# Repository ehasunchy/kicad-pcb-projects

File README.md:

# KiCad PCB Design Portfolio

## Featured Project — ESP32 IoT Sensor Controller

A custom-designed, two-layer ESP32 IoT controller PCB
developed in KiCad 10, integrating an ESP32-WROOM-32E,
SHT31 temperature and humidity sensor, CP2102N
USB-to-UART interface, and regulated 3.3V power supply.

**Highlights:**
- Complete schematic and PCB layout
- ERC and DRC passed with 0 errors and 0 warnings
- Fully routed PCB with 0 unrouted connections
- Gerber X2, drill files, component position files, and BOM included
- Design completed; fabrication and physical testing pending

**[Explore the ESP32 IoT Sensor Controller Project](ESP32_IoT_Sensor_Controller/README.md)**

---

**LED indicators · Voltage regulation · NE555 timer · USB-C power · Schematic-to-PCB workflow**

Five PCB design projects, ranging from basic LED circuits and voltage regulators to an ESP32-based IoT sensor controller, with editable KiCad sources, design previews, and available manufacturing documentation.

## Projects

| Project | Scope |
| :--- | :--- |
| [ESP32 IoT Sensor Controller](ESP32_IoT_Sensor_Controller/README.md) | Two-layer ESP32 IoT PCB featuring SHT31 sensing, CP2102N USB-UART, 3.3V regulation, design verification, BOM, and manufacturing outputs. |
| [LED Basic Board](LED_Basic_Board/README.md) | A three-footprint LED indicator practice board with a 330-ohm resistor and two-pin connector. |
| [5V to 3V3 LDO Board](5V_to_3V3_LDO_Board/README.md) | A seven-footprint AMS1117-3.3 regulator practice board with capacitors, input/output connectors, and an LED indicator. |
| [NE555 Astable LED Blinker](555_Timer_LED_Blinker/README.md) | A 5V timer-based LED blinker with editable source, Gerbers, drill exports, and previews. |
| [USB-C 3.3V Interface Board](USB_C_3V3_Interface_Board/README.md) | A USB-C-powered AP2112K-3.3 regulator board with I²C/GPIO headers, BOM, manufacturing outputs and current checks with disclosed exclusions. |

## Open a design

Open the corresponding `.kicad_pro` in KiCad 10.0. Open KiCad_Project/ inside the selected project. Supplied Gerbers and drill files are browsable under Manufacturing/, with unchanged original complete ZIPs under Archives/.

## Use and validation

Open editable project files in their original CAD application. The archives preserve project subfolders; extract an archive before opening its project. External libraries or 3D-model paths may need to be remapped on another computer.

These are portfolio design files. Existing reports are snapshots from their recorded dates; fabrication exports are not evidence of manufactured or bench-tested hardware. Review the design and rerun the checks before fabrication.

No blanket license is assigned. Third-party components, libraries, and tutorial material retain their original rights and terms.

## Repository organization

Each project guide links to its editable sources, available outputs and recorded status. Original project archives remain unchanged. [Reorganization record](Documentation/REORGANIZATION.md) documents preservation and path changes.

## Related portfolios

- [KiCad PCB projects](https://github.com/ehasunchy/kicad-pcb-projects)
- [Altium PCB projects](https://github.com/ehasunchy/altium-pcb-projects)
- [AutoCAD Electrical projects](https://github.com/ehasunchy/autocad-electrical-projects)

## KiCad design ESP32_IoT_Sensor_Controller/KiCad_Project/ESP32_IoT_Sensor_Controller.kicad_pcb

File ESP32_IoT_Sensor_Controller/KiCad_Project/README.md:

# KiCad Source Files

This folder contains the editable KiCad 10 project files for the ESP32 IoT Sensor Controller, including the schematic, PCB layout, project configuration, and custom symbol and footprint libraries.

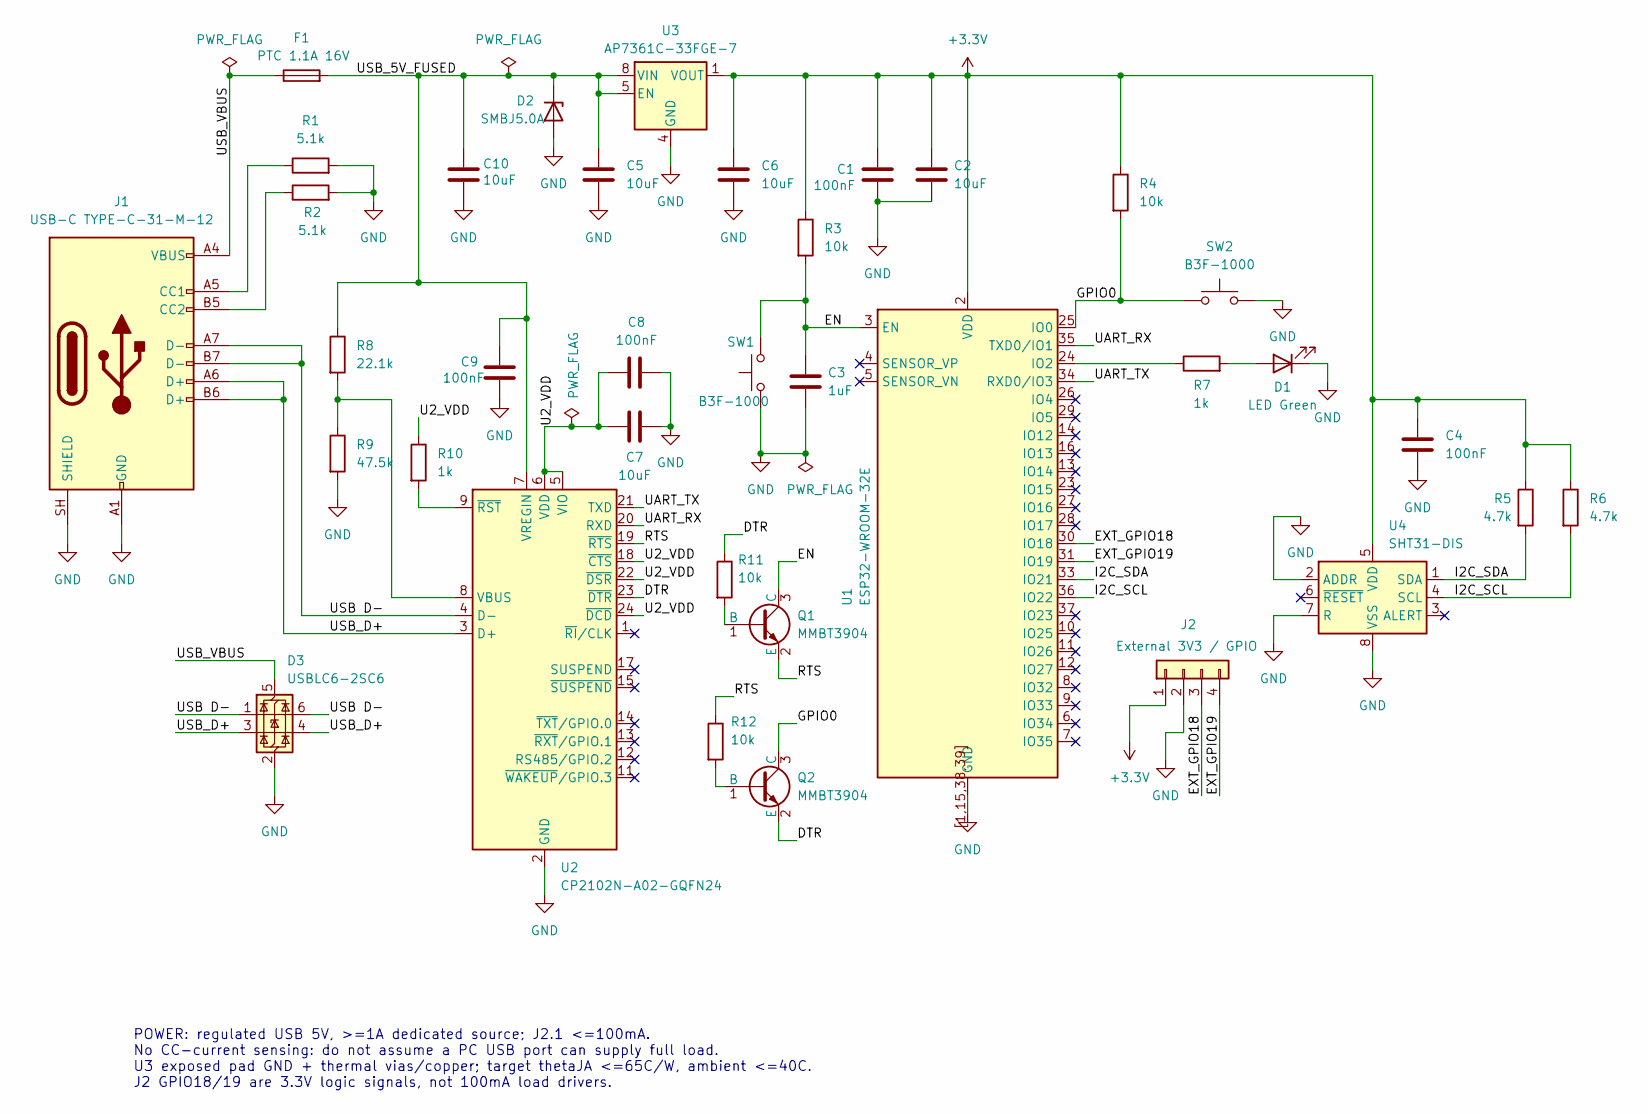
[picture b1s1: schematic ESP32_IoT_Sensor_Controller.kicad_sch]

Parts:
C1, C4, C8, C9: 100nF; C_0603_1608Metric; Rating 50V X7R +/-10%; MPN C1608X7R1H104K080AA
C2, C5, C6, C7: 10uF; C_1206_3216Metric; Rating 25V X7R +/-10%; verify effective >=4.7u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; MPN CL31B106KAHNNNE
C3: 1uF; C_0603_1608Metric; Rating 10V X5R +/-10%; MPN C1608X5R1A105K080AC
C10: 10uF; C_1206_3216Metric; Rating 25V X7R +/-10%; local VREGIN bulk; MPN CL31B106KAHNNNE
D1: LED Green; LED_0603_1608Metric; Rating 0603 1K 2A; MPN APT1608SGC
D2: SMBJ5.0A; D_SMB; Rating 5V standoff; ESD/surge only, NOT sustai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; MPN SMBJ5.0A-TR
D3: USBLC6-2SC6; SOT-23-6; Rating SOT23-6 USB ESD; MPN USBLC6-2SC6
F1: PTC 1.1A 16V; Fuse_1206_3216Metric; Rating Ihold1.1A at20C; 0.92A at40C; MPN 1206L110/16WR
J1: USB-C TYPE-C-31-M-12; USB_C_HRO_Custom; Rating USB2.0 16-contact; A8/B8 unused; MPN TYPE-C-31-M-12
J2: External 3V3 / GPIO; PinHeader_1x04_P2.54mm_Vertical; Rating 2.54mm 1x4; J2.1 max100mA, GPIO only si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; MPN TSW-104-07-G-S
Q1, Q2: MMBT3904; SOT-23; Rating SOT23 1B 2E 3C; MPN MMBT3904LT1G
R1, R2: 5.1k; R_0603_1608Metric; Rating 1% 0.1W 0603; MPN RC0603FR-075K1L
R3, R4, R11, R12: 10k; R_0603_1608Metric; Rating 1% 0.1W 0603; MPN RC0603FR-0710KL
R5, R6: 4.7k; R_0603_1608Metric; Rating 1% 0.1W 0603; MPN RC0603FR-074K7L
R7, R10: 1k; R_0603_1608Metric; Rating 1% 0.1W 0603; MPN RC0603FR-071KL
R8: 22.1k; R_0603_1608Metric; Rating 1% 0.1W 0603; MPN RC0603FR-0722K1L
R9: 47.5k; R_0603_1608Metric; Rating 1% 0.1W 0603; MPN RC0603FR-0747K5L
SW1, SW2: B3F-1000; SW_PUSH_6mm; Rating SPST-NO; same-net pairs 1/1 and 2/2; MPN B3F-1000
U1: ESP32-WROOM-32E; ESP32-WROOM-32E_Custom; Rating 4MB flash PCB antenna; MPN ESP32-WROOM-32E-N4
U2: CP2102N-A02-GQFN24; QFN24_4x4mm_P0.5mm_CP2102N; Rating QFN24 EP25 GND; MPN CP2102N-A02-GQFN24R
U3: AP7361C-33FGE-7; AP7361C_UDFN3030_8E; Rating 3.3V 1A; thermal copper and vias requir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; MPN AP7361C-33FGE-7
U4: SHT31-DIS; Sensirion_DFN-8-1EP_2.5x2.5mm_P0.5mm_EP1.1x1.7mm; Rating DFN8 EP9 GND; I2C address 0x44; MPN SHT31-DIS-B

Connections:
+3.3V: C1.1, C2.1, C4.1, C6.1, J2.1, R3.1, R4.1, R5.1, R6.1, U1.2 (VDD), U3.1 (VOUT), U4.5 (VDD)
/DTR: Q2.2 (E), R11.1, U2.23 (~DTR)
/EN: C3.1, Q1.3 (C), R3.2, SW1.2, U1.3 (EN)
/EXT_GPIO18: J2.3, U1.30 (IO18)
/EXT_GPIO19: J2.4, U1.31 (IO19)
/GPIO0: Q2.3 (C), R4.2, SW2.1, U1.25 (IO0)
/I2C_SCL: R6.2, U1.36 (IO22), U4.4 (SCL)
/I2C_SDA: R5.2, U1.33 (IO21), U4.1 (SDA)
/RTS: Q1.2 (E), R12.1, U2.19 (~RTS)
/U2_VDD: C7.1, C8.1, R10.1, U2.5 (VIO), U2.6 (VDD), U2.18 (~CTS), U2.22 (~DSR), U2.24 (~DCD)
/UART_RX: U1.35 (TXD0/IO1), U2.20 (RXD)
/UART_TX: U1.34 (RXD0/IO3), U2.21 (TXD)
/USB D−: D3.1 (I/O1), D3.6 (I/O1), J1.A7 (D-), J1.B7 (D-), U2.4 (D-)
/USB_5V_FUSED: C5.1, C9.1, C10.1, D2.1 (K), F1.2, R8.1, U2.7 (VREGIN), U3.5 (EN), U3.8 (VIN)
/USB_D+: D3.3 (I/O2), D3.4 (I/O2), J1.A6 (D+), J1.B6 (D+), U2.3 (D+)
/USB_VBUS: D3.5 (VBUS), F1.1, J1.A4 (VBUS), J1.A9 (VBUS), J1.B4 (VBUS), J1.B9 (VBUS)
GND: C1.2, C2.2, C3.2, C4.2, C5.2, C6.2, C7.2, C8.2, C9.2, C10.2, D1.1 (K), D2.2 (A), D3.2 (GND), J1.A1 (GND), J1.A12 (GND), J1.B1 (GND), J1.B12 (GND), J1.SH (SHIELD), J2.2, R1.2, R2.2, R9.2, SW1.1, SW2.2, U1.1 (GND), U1.15 (GND), U1.38 (GND), U1.39 (GND), U1.[1,15,38,39] (GND), U2.2 (GND), U2.25 (GND), U3.4 (GND), U3.9 (EP_GND), U4.2 (ADDR), U4.7 (R), U4.8 (VSS), U4.9 (VSS)
unnamed: D1.2 (A), R7.2
unnamed: J1.A5 (CC1), R1.1
unnamed: J1.B5 (CC2), R2.1
unnamed: Q1.1 (B), R11.2
unnamed: Q2.1 (B), R12.2
unnamed: R7.1, U1.24 (IO2)
unnamed: R8.2, R9.1, U2.8 (VBUS)
unnamed: R10.2, U2.9 (~RST)

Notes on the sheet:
POWER: regulated USB 5V, >=1A dedicated source; J2.1 <=100mA. No CC-current sensing: do not assume a PC USB port can supply full load. U3 exposed pad GND + thermal vias/copper; target thetaJA <=65C/W, ambient <=40C. J2 GPIO18/19 are 3.3V logic signals, not 100mA load drivers.

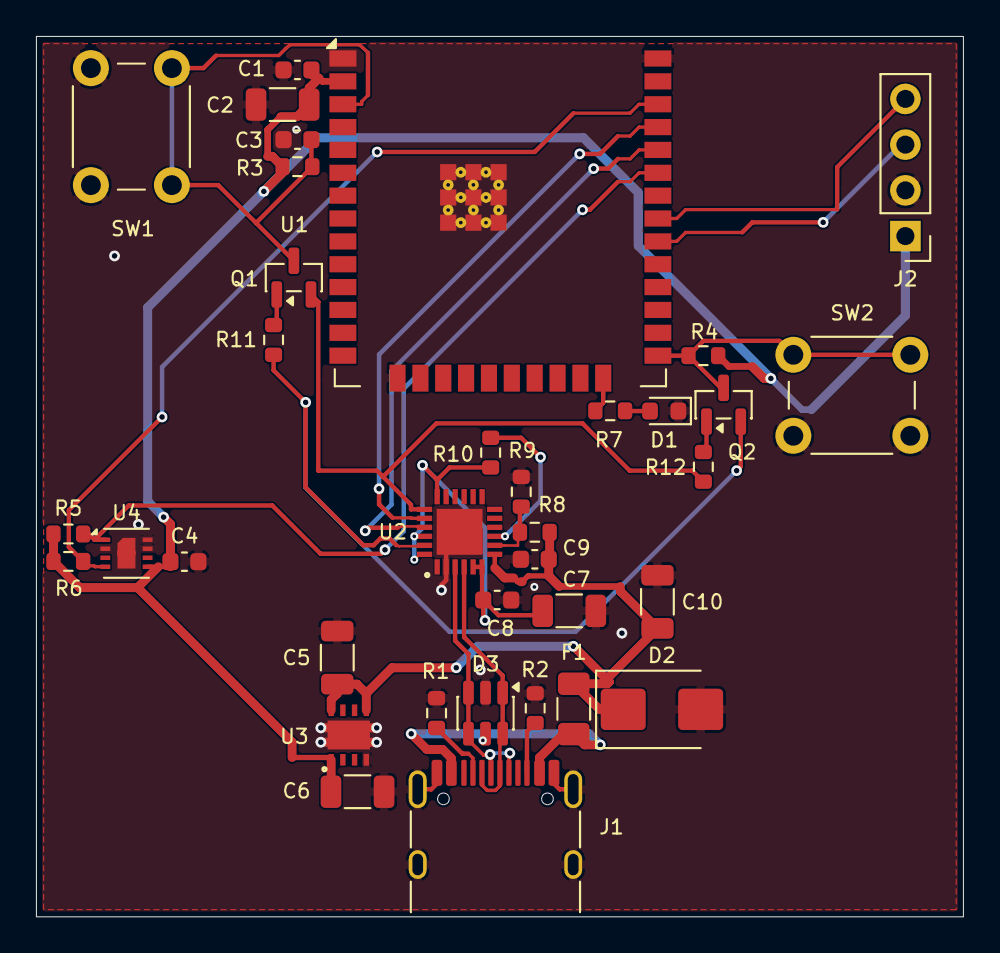
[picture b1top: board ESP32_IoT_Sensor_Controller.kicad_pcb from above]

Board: 2 copper layers, 51.5 x 48.9 mm, 36 parts (0 on the bottom side), 25 nets.

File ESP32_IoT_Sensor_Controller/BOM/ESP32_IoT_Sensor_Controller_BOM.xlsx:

ESP32 IoT Sensor Controller — Bill of Materials
Project: ESP32_IoT_Sensor_Controller
Design Tool: KiCad 10 | PCB: 2-Layer
Status: Design completed; manufacturing and physical testing pending
Total quantity / board | 36
Reference | Qty | Value | Footprint | Datasheet | Manufacturer | MPN
C1,C4,C8,C9 | 4 | 100nF | Capacitor_SMD:C_0603_1608Metric | Datasheet | TDK | C1608X7R1H104K080AA
C2,C5,C6,C7,C10 | 5 | 10uF | Capacitor_SMD:C_1206_3216Metric | Datasheet | Samsung Electro-Mechanics | CL31B106KAHNNNE
C3 | 1 | 1uF | Capacitor_SMD:C_0603_1608Metric | Datasheet | TDK | C1608X5R1A105K080AC
D1 | 1 | LED Green | LED_SMD:LED_0603_1608Metric | Datasheet | Kingbright | APT1608SGC
D2 | 1 | SMBJ5.0A | Diode_SMD:D_SMB | Datasheet | STMicroelectronics | SMBJ5.0A-TR
D3 | 1 | USBLC6-2SC6 | Package_TO_SOT_SMD:SOT-23-6 | Datasheet | STMicroelectronics | USBLC6-2SC6
F1 | 1 | PTC 1.1A 16V | Fuse:Fuse_1206_3216Metric | Datasheet | Littelfuse | 1206L110/16WR
J1 | 1 | USB-C TYPE-C-31-M-12 | ESP32_IoT_Custom:USB_C_HRO_Custom | Datasheet | HRO | TYPE-C-31-M-12
J2 | 1 | External 3V3 / GPIO | Connector_PinHeader_2.54mm:PinHeader_1x04_P2.54mm_Vertical | Datasheet | Samtec | TSW-104-07-G-S
Q1,Q2 | 2 | MMBT3904 | Package_TO_SOT_SMD:SOT-23 | Datasheet | onsemi | MMBT3904LT1G
R1,R2 | 2 | 5.1k | Resistor_SMD:R_0603_1608Metric | Datasheet | YAGEO | RC0603FR-075K1L
R3,R4,R11,R12 | 4 | 10k | Resistor_SMD:R_0603_1608Metric | Datasheet | YAGEO | RC0603FR-0710KL
R5,R6 | 2 | 4.7k | Resistor_SMD:R_0603_1608Metric | Datasheet | YAGEO | RC0603FR-074K7L
R7,R10 | 2 | 1k | Resistor_SMD:R_0603_1608Metric | Datasheet | YAGEO | RC0603FR-071KL
R8 | 1 | 22.1k | Resistor_SMD:R_0603_1608Metric | Datasheet | YAGEO | RC0603FR-0722K1L
R9 | 1 | 47.5k | Resistor_SMD:R_0603_1608Metric | Datasheet | YAGEO | RC0603FR-0747K5L
SW1,SW2 | 2 | B3F-1000 | Button_Switch_THT:SW_PUSH_6mm | Datasheet | Omron | B3F-1000
U1 | 1 | ESP32-WROOM-32E | ESP32_IoT_Custom:ESP32-WROOM-32E_Custom | Datasheet | Espressif | ESP32-WROOM-32E-N4
U2 | 1 | CP2102N-A02-GQFN24 | Controller:QFN24_4x4mm_P0.5mm_CP2102N | Datasheet | Silicon Labs | CP2102N-A02-GQFN24R
U3 | 1 | AP7361C-33FGE-7 | Controller:AP7361C_UDFN3030_8E | Datasheet | Diodes Incorporated | AP7361C-33FGE-7
U4 | 1 | SHT31-DIS | Sensor_Humidity:Sensirion_DFN-8-1EP_2.5x2.5mm_P0.5mm_EP1.1x1.7mm | Datasheet | Sensirion | SHT31-DIS-B
0 | 0 | 0 | 0 |  | 0 | 0
0 | 0 | 0 | 0 |  | 0 | 0
0 | 0 | 0 | 0 |  | 0 | 0
0 | 0 | 0 | 0 |  | 0 | 0
0 | 0 | 0 | 0 |  | 0 | 0
0 | 0 | 0 | 0 |  | 0 | 0
0 | 0 | 0 | 0 |  | 0 | 0
0 | 0 | 0 | 0 |  | 0 | 0
0 | 0 | 0 | 0 |  | 0 | 0

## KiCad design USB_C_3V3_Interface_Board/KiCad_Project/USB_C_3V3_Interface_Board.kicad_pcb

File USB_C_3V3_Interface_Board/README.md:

# USB-C 3.3V Interface Board

**A compact two-layer KiCad practice PCB for USB-C 5V power input, nominal 3.3V regulation and I²C/GPIO header connections.**

## Project overview

The board accepts nominal 5V power through a USB-C receptacle and uses an AP2112K-3.3 LDO to supply external low-power electronics. Separate 5.1kΩ CC pull-down resistors implement a USB-C power sink. USB data transfer and USB Power Delivery negotiation are not implemented.

The I²C and GPIO headers provide connections only. There is no onboard microcontroller or I²C controller. SDA/SCL each have a 4.7kΩ pull-up to 3.3V; GPIO1/GPIO2 each terminate at a single header pin and are not driven on this board.

## Technical specifications

| Parameter | Specification |
| :--- | :--- |
| CAD application | KiCad 10.0; exports/checks generated with 10.0.6 |
| Board outline | 22 × 25.5 mm, measured between outline centerlines |
| Copper layers | 2: F.Cu and B.Cu |
| Nominal input | 5V DC via USB-C |
| Nominal regulated output | 3.3V DC |
| Regulator | AP2112K-3.3 |
| Input protection components | 500mA-rated resettable polyfuse and PESD5V0S1UA TVS |
| Interfaces | Two 1×4 headers for I²C and GPIO connections |
| Layout | Top-side components/routing and bottom-layer GND copper zone |
| Manufacturing outputs | Seven Gerbers, PTH/NPTH Excellon drills and Gerber job file |

The fuse rating does not establish a guaranteed continuous output current. Available output current depends on regulator dissipation, PCB thermal conditions, ambient temperature and component ratings.

## Main components

| Reference | Component/value | Purpose |
| :--- | :--- | :--- |
| J1 | GCT USB4105 USB-C receptacle | Power input |
| R1, R2 | 5.1kΩ | CC1/CC2 pull-down resistors |
| F1 | 500mA resettable polyfuse | Input protection component |
| D1 | PESD5V0S1UA | TVS protection component |
| U1 | AP2112K-3.3 | Nominal 3.3V regulation |
| C1, C2 | 1µF | Input/output decoupling |
| R3, D2 | 1kΩ and green LED | Power indication |
| R4, R5 | 4.7kΩ | SDA/SCL pull-ups |
| J2, J3 | 1×4, 2.54mm headers | External connections |

[BOM CSV](BOM/USB_C_3V3_Interface_Board.csv) contains ten grouped rows covering fourteen components, including footprints and manufacturer/MPN fields. Values, quantities, references and fields were checked against the exported schematic netlist. These checks do not establish component availability or suitability for every operating condition.

## Connector pinouts

| Pin | J2 — I²C | J3 — GPIO |
| :---: | :--- | :--- |
| 1 | +3V3 | +3V3 |
| 2 | GND | GND |
| 3 | SDA | GPIO1 |
| 4 | SCL | GPIO2 |

Pinouts were checked against the schematic netlist. Use the source schematic when connecting external hardware.

## Project files

| Folder | Contents |
| :--- | :--- |
| [KiCad_Project](KiCad_Project/) | Editable project, schematic and PCB |
| [Images](Images/) | Schematic SVG, large top/bottom layout PNG/SVG and 3D preview |
| [Reports](Reports/README.md) | Current ERC/DRC JSON and validation notes |
| [BOM](BOM/USB_C_3V3_Interface_Board.csv) | Component list |
| [Manufacturing](Manufacturing/README.md) | Supplied Gerber/drill exports and download package |
| [Archives](Archives/) | Source/BOM/manufacturing snapshot ZIP |

Open [USB_C_3V3_Interface_Board.kicad_pro](KiCad_Project/USB_C_3V3_Interface_Board.kicad_pro) in KiCad 10.0. Footprints and 3D models use standard KiCad libraries; preview renders depend on the installed model libraries. Temporary lock files, local UI preferences and editor history are not part of the portfolio upload.

## Design verification — 2026-10-09

- [DRC](Reports/DRC.json): zero non-excluded violations, zero unconnected items and zero schematic-parity findings under the saved project settings. **Four excluded USB-C pad-to-NPTH hole-clearance errors remain**: actual clearance 0.1944mm versus the configured 0.2500mm requirement.
- [ERC](Reports/ERC.json): zero error-severity records. The all-severity export contains four warning records for two unique GPIO label findings: GPIO1/GPIO2 each appear once normally and once as excluded. These signals each connect to only one header pin. This is disclosed rather than presented as a zero-warning ERC result.
- Reports include the saved settings' ignored-check lists. Exclusions and disabled checks limit the scope of a clean result.
- BOM fields and header pinouts were compared with the source netlist. Schematic, PCB and 3D previews were generated from the saved source snapshot.

No physical fabrication, assembly, load testing, thermal testing or ESD testing is documented. The connector hole clearances require fabrication review. TVS working/clamping voltage and regulator thermal capability still require operating-condition validation. Manufacturing outputs are supplied exports, not a fabrication approval.

## Project images

### Schematic

### PCB layout

[Zoomable top SVG](Images/pcb-layout.svg)

[Zoomable bottom SVG](Images/pcb-layout-bottom.svg)

Top and bottom copper are shown separately so the bottom ground fill does not cover top routing. The bottom view is mirrored to represent looking from below. Both layout PNGs are 1000 × 1280 pixels; SVG versions retain scalable detail. The 3D image above is a generated preview, not a photograph of assembled hardware.

## Author

**Ehasan Alam Chowdhury** — Electrical & Electronic Engineering (EEE)

GitHub: [ehasunchy](https://github.com/ehasunchy)

Part of a practical PCB design portfolio. [Return to the KiCad portfolio](../README.md).

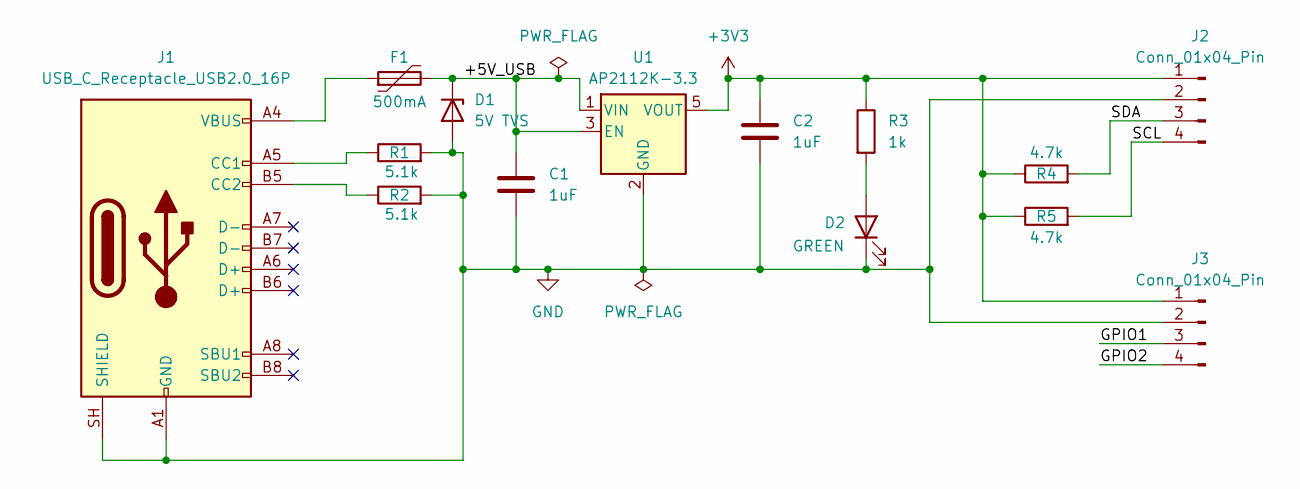
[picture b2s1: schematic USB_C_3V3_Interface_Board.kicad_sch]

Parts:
C1, C2: 1uF; C_0805_2012Metric; MPN GRM21BR71C105KA01L
D1: 5V TVS; D_SOD-323; MPN PESD5V0S1UA,115
D2: GREEN; LED_0805_2012Metric; MPN APT2012LZGCK
F1: 500mA; Fuse_1206_3216Metric; MPN 1206L050/15YR
J1: USB_C_Receptacle_USB2.0_16P; USB_C_Receptacle_GCT_USB4105-xx-A_16P_TopMnt_Horizontal; MPN USB4105-GF-A-120
J2, J3: Conn_01x04_Pin; PinHeader_1x04_P2.54mm_Vertical; MPN 61300411121
R1, R2: 5.1k; R_0805_2012Metric; MPN RC0805FR-075K1L
R3: 1k; R_0805_2012Metric; MPN RC0805FR-071KL
R4, R5: 4.7k; R_0805_2012Metric; MPN RC0805FR-074K7L
U1: AP2112K-3.3; SOT-23-5; MPN AP2112K-3.3TRG1

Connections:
+3V3: C2.1, J2.1, J3.1, R3.1, R4.1, R5.1, U1.5 (VOUT)
/+5V_USB: C1.1, D1.1 (K), F1.2, U1.1 (VIN), U1.3 (EN)
/GPIO1: J3.3
/GPIO2: J3.4
/SCL: J2.4, R5.2
/SDA: J2.3, R4.2
GND: C1.2, C2.2, D1.2 (A), D2.1 (K), J1.A1 (GND), J1.A12 (GND), J1.B1 (GND), J1.B12 (GND), J1.SH (SHIELD), J2.2, J3.2, R1.2, R2.2, U1.2 (GND)
unnamed: D2.2 (A), R3.2
unnamed: F1.1, J1.A4 (VBUS), J1.A9 (VBUS), J1.B4 (VBUS), J1.B9 (VBUS)
unnamed: J1.A5 (CC1), R1.1
unnamed: J1.B5 (CC2), R2.1

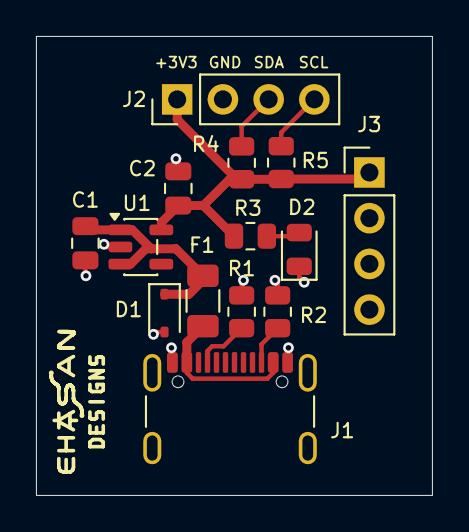
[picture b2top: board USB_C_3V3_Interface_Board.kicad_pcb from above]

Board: 2 copper layers, 22.0 x 25.5 mm, 14 parts (0 on the bottom side), 9 nets.

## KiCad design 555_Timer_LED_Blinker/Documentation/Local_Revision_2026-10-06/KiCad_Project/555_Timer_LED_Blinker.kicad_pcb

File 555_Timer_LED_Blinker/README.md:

# NE555 Astable LED Blinker

A 5V LED blinker designed in KiCad 10.0 using an NE555P timer in astable mode. The schematic includes a 10k/100k timing resistor network, a 10uF timing capacitor, a 1k LED resistor, 100uF supply decoupling, and 10nF control-pin bypassing.

## Files

- Editable KiCad project, schematic, and PCB source files in the project source folder
- [Complete project archive](Archives/555_Timer_LED_Blinker.zip), including the supplied Gerber and drill exports
- PNG and SVG previews generated from the source with KiCad 10.0

## Design status

The preserved KiCad 10.0.6 reports dated 2026-10-05 reported **0 DRC violations, 0 unconnected items, 0 schematic parity issues, and 0 ERC violations** under the supplied project settings. The JSON reports record ignored checks and included severities; this does not establish hardware testing. The supplied fabrication exports are preserved as provided.

- [DRC report](Reports/555_Timer_LED_Blinker-DRC.json)
- [ERC report](Reports/555_Timer_LED_Blinker-ERC.json)

## Browse this project

Open [555_Timer_LED_Blinker.kicad_pro](KiCad_Project/555_Timer_LED_Blinker.kicad_pro) in KiCad 10. Download or clone the whole repository to keep related files together.

| Folder | Contents |
| :--- | :--- |
| [Archives/](Archives/) | Unchanged original complete project ZIP |
| [Documentation/](Documentation/) | Supporting documentation and preserved source-reference snapshots |
| [Images/](Images/) | Existing schematic and board previews |
| [KiCad_Project/](KiCad_Project/) | Editable project, schematic and PCB files |
| [Manufacturing/](Manufacturing/) | Existing fabrication, drill and assembly outputs |
| [Reports/](Reports/) | Saved design-check reports |

## BOM and later local manufacturing revision

The recovered [BOM CSV](BOM/555_Timer_LED_Blinker.csv) contains 9 grouped rows and 10 components, including J1/J2 grouped as quantity 2. Manufacturer and MPN fields are supplied project metadata; purchasing suitability is not established.

The OneDrive local revision has added schematic BOM fields and changes to the PCB outline, capacitor placement and routing. It is preserved as a separate [local source snapshot](Documentation/Local_Revision_2026-10-06/KiCad_Project/) with its [local Gerber/drill files](Manufacturing/Local_Revision_2026-10-06/Gerbers/). The primary `KiCad_Project/`, previews and 2026-10-05 reports remain the existing GitHub revision. The old reports do not validate the later local revision. See [manufacturing documentation](Manufacturing/README.md) before choosing an output set.

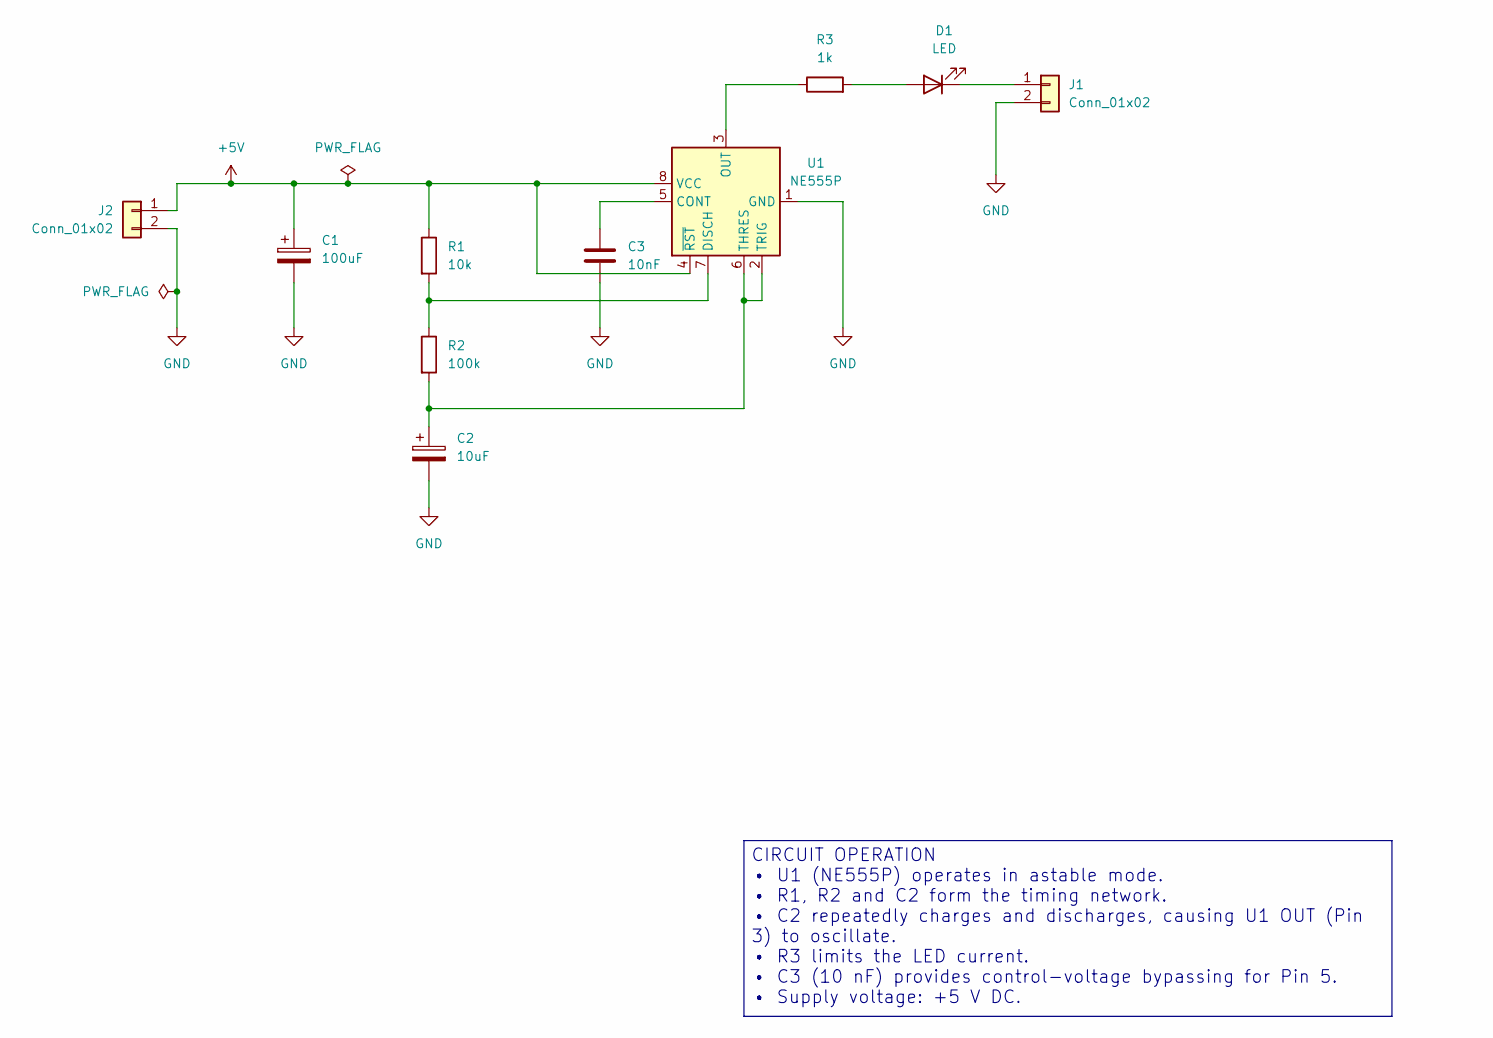
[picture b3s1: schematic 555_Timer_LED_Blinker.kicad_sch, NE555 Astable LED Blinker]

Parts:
C1: 100uF; CP_Elec_6.3x5.8; MPN UWT0J101MCL1GB
C2: 10uF; CP_Elec_4x5.8; MPN UWT1C100MCL1GB
C3: 10nF; C_0805_2012Metric; MPN CC0805KRX7R9BB103
D1: LED; LED_0805_2012Metric; MPN APT2012SURCK
J1, J2: Conn_01x02; PinHeader_1x02_P2.54mm_Vertical; MPN 61300211121
R1: 10k; R_0805_2012Metric; MPN RC0805FR-0710KL
R2: 100k; R_0805_2012Metric; MPN RC0805FR-07100KL
R3: 1k; R_0805_2012Metric; MPN RC0805FR-071KL
U1: NE555P; DIP-8_W7.62mm; MPN NE555P

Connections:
+5V: C1.1, J2.1, R1.1, U1.4 (~RST), U1.8 (VCC)
GND: C1.2, C2.2, C3.2, J1.2, J2.2, U1.1 (GND)
unnamed: D1.2 (A), R3.2
unnamed: D1.1 (K), J1.1
unnamed: C3.1, U1.5 (CONT)
unnamed: R1.2, R2.1, U1.7 (DISCH)
unnamed: R3.1, U1.3 (OUT)
unnamed: C2.1, R2.2, U1.2 (TRIG), U1.6 (THRES)

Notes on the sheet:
CIRCUIT OPERATION • U1 (NE555P) operates in astable mode. • R1, R2 and C2 form the timing network. • C2 repeatedly charges and discharges, causing U1 OUT (Pin 3) to oscillate. • R3 limits the LED current. • C3 (10 nF) provides control-voltage bypassing for Pin 5. • Supply voltage: +5 V DC.

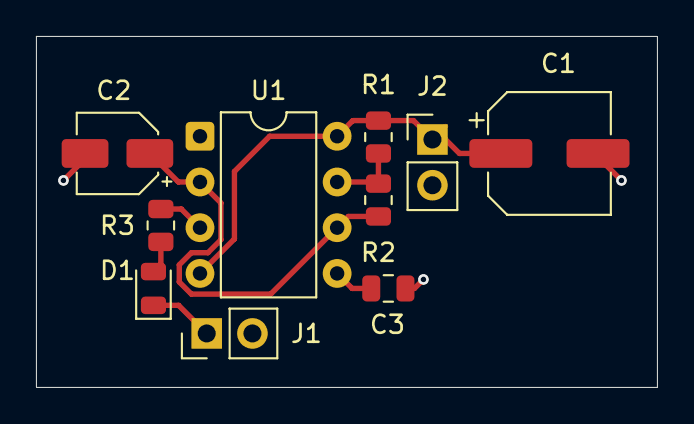
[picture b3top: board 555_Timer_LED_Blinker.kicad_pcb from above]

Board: 2 copper layers, 34.5 x 19.5 mm, 10 parts (0 on the bottom side), 8 nets.

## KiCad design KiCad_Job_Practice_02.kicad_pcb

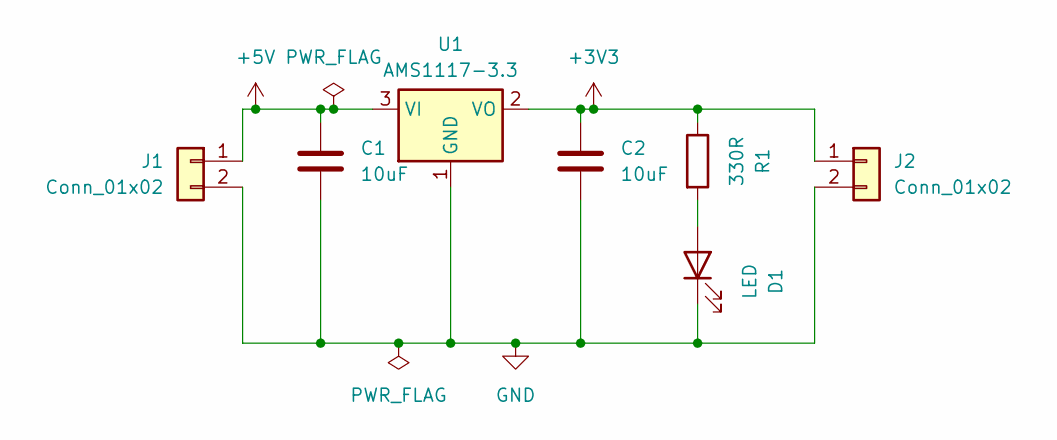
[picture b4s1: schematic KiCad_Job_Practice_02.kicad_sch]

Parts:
C1, C2: 10uF; C_0805_2012Metric
D1: LED; LED_0805_2012Metric
J1, J2: Conn_01x02; PinHeader_1x02_P2.54mm_Vertical
R1: 330R; R_0805_2012Metric
U1: AMS1117-3.3; SOT-223-3_TabPin2

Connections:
+3V3: C2.1, J2.1, R1.1, U1.2 (VO)
+5V: C1.1, J1.1, U1.3 (VI)
GND: C1.2, C2.2, D1.1 (K), J1.2, J2.2, U1.1 (GND)
unnamed: D1.2 (A), R1.2

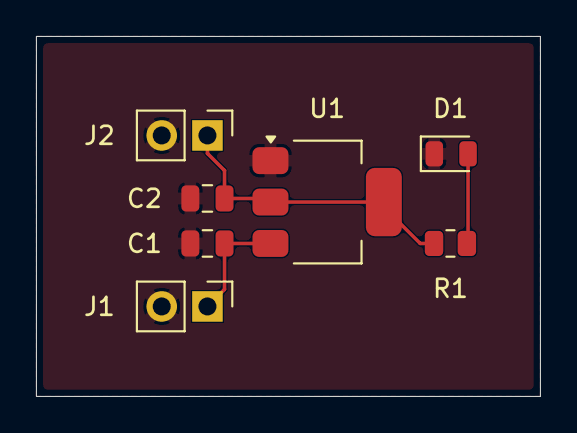
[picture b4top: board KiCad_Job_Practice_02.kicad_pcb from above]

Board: 2 copper layers, 28.0 x 20.0 mm, 7 parts (0 on the bottom side), 4 nets.

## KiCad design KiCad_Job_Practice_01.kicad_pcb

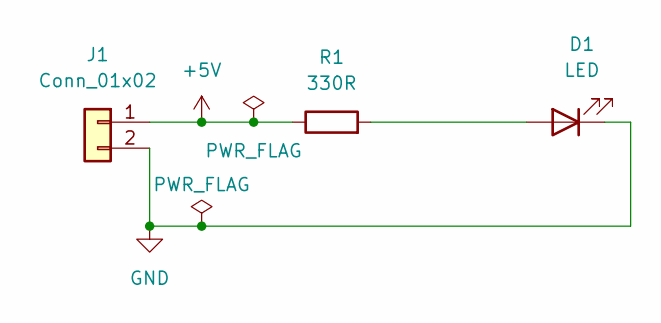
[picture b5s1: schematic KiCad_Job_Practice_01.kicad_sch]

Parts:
D1: LED; LED_D5.0mm
J1: Conn_01x02; PinHeader_1x02_P2.54mm_Vertical
R1: 330R; R_Axial_DIN0207_L6.3mm_D2.5mm_P10.16mm_Horizontal

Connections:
+5V: J1.1, R1.1
GND: D1.1 (K), J1.2
unnamed: D1.2 (A), R1.2

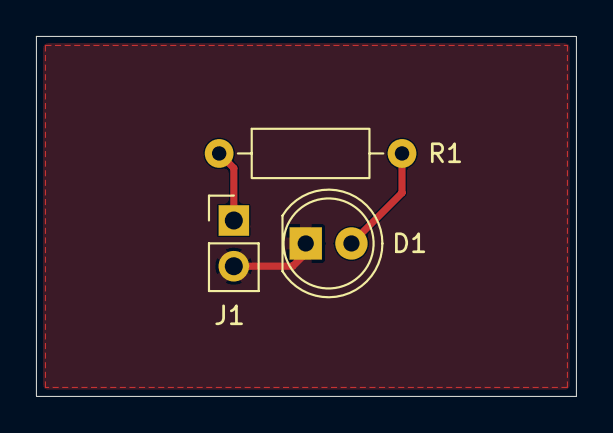
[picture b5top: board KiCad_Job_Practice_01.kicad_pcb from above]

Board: 2 copper layers, 30.0 x 20.0 mm, 3 parts (0 on the bottom side), 3 nets.
